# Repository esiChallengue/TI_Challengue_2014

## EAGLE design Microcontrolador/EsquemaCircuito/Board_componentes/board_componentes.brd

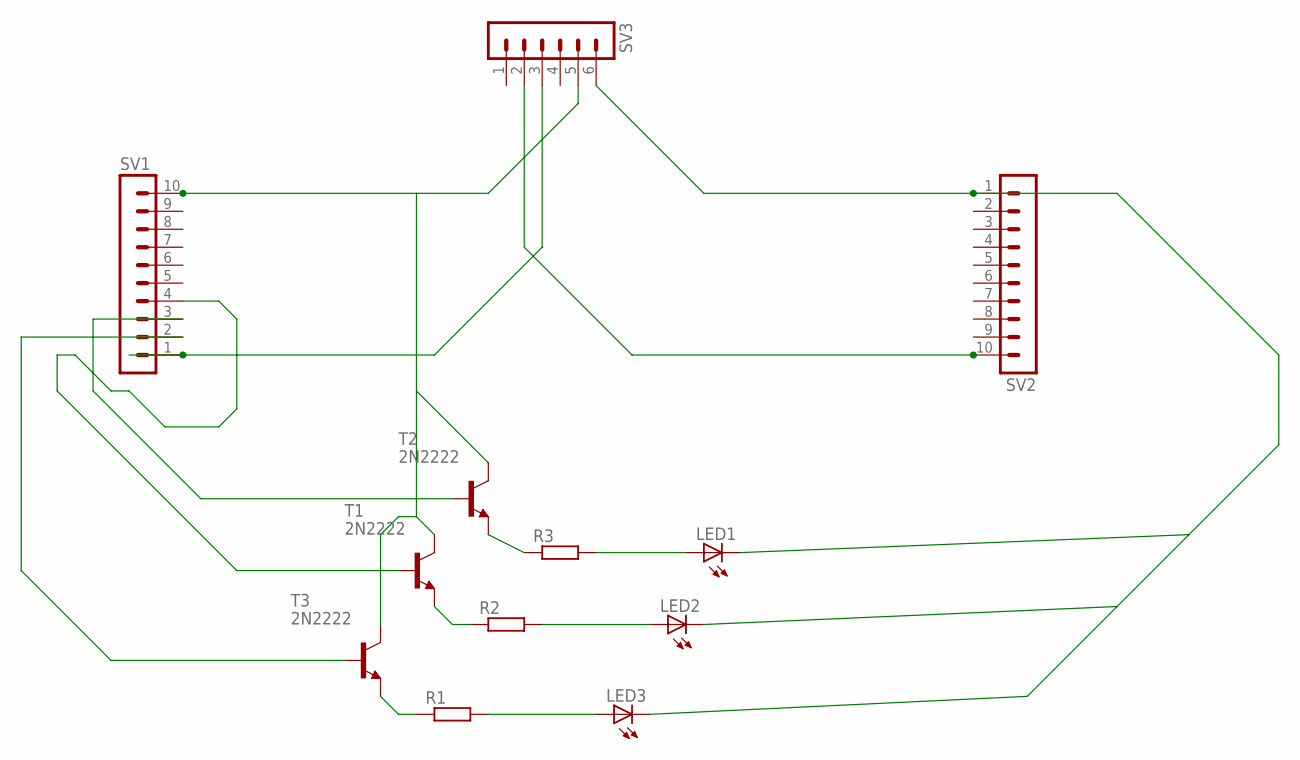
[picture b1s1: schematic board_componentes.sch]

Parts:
LED1, LED2, LED3: LED_ELD260; LED_LD260
R1, R2, R3: R-EU_0207/12; 0207/12
SV1, SV2: MA10-1
SV3: MA06-1
T1, T2, T3: 2N2222; TO18

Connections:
unnamed: LED1.K (C), LED2.K (C), LED3.K (C), SV2.1, SV3.6
unnamed: SV1.10, SV3.5, T1.3 (C), T2.3 (C), T3.3 (C)
unnamed: SV1.4, T1.2 (B)
unnamed: SV1.2, T3.2 (B)
unnamed: SV1.3, T2.2 (B)
unnamed: SV2.10, SV3.2
unnamed: R1.1, T3.1 (E)
unnamed: LED3.A, R1.2
unnamed: SV1.1, SV3.3
unnamed: LED1.A, R3.2
unnamed: LED2.A, R2.2
unnamed: R2.1, T1.1 (E)
unnamed: R3.1, T2.1 (E)

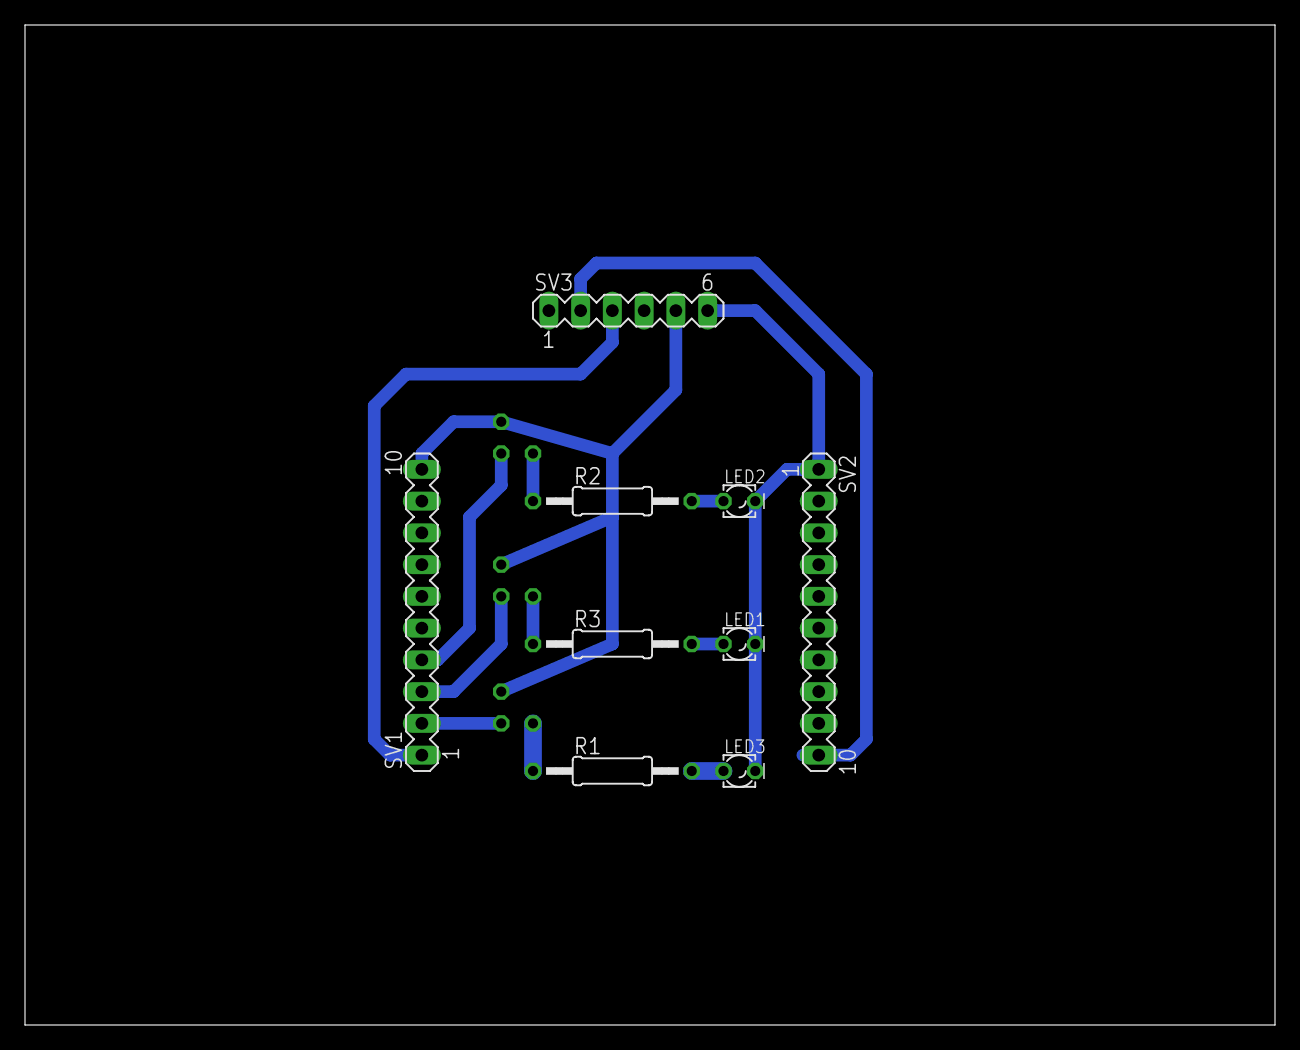
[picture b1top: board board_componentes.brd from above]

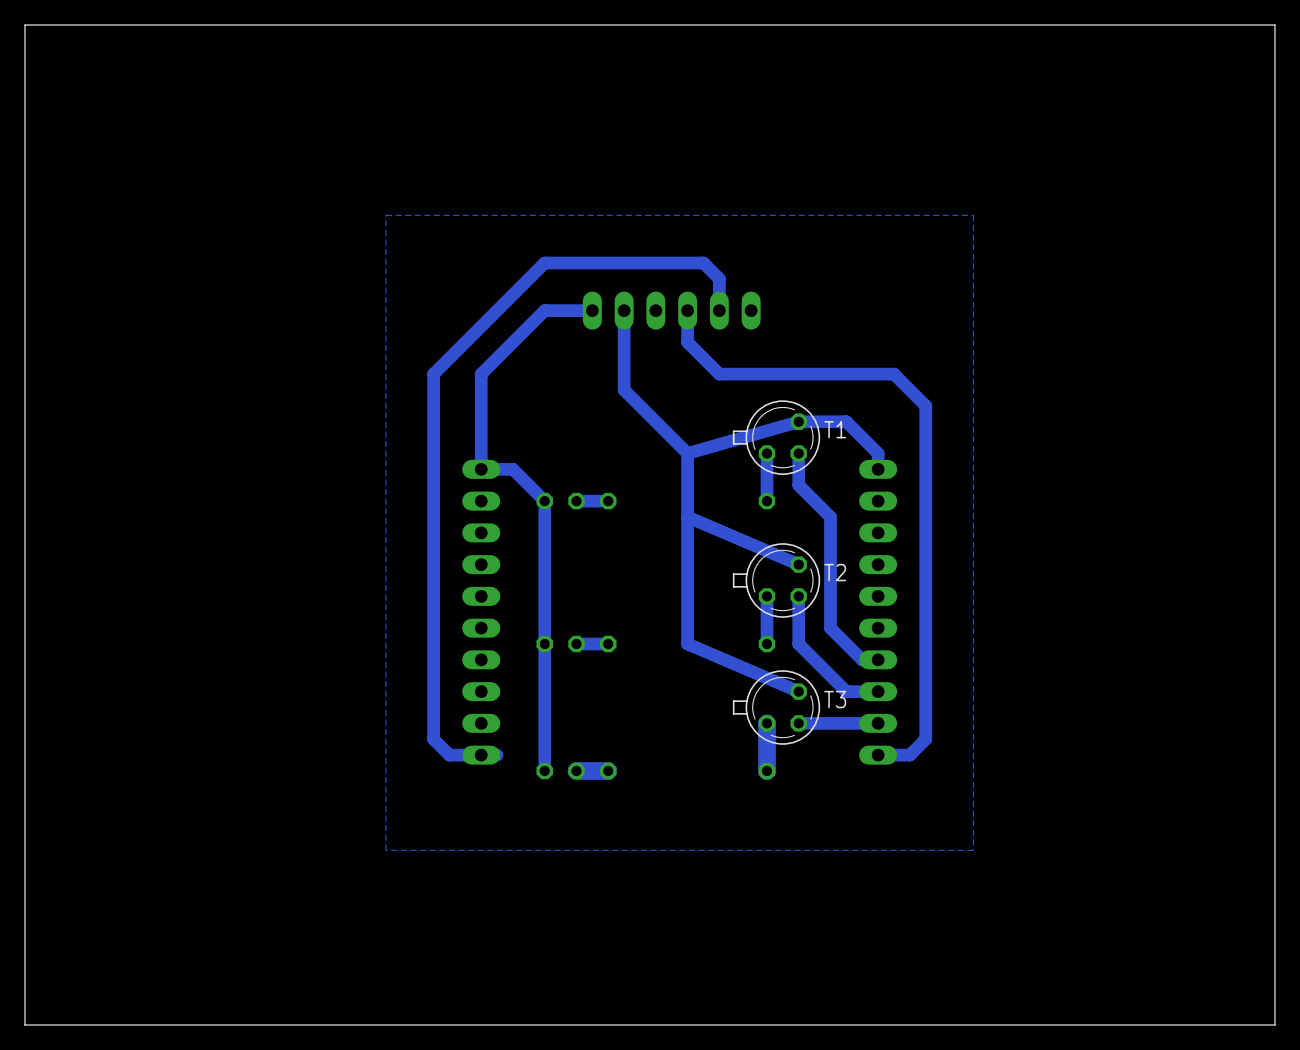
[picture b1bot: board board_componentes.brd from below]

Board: 2 copper layers, 100.0 x 80.0 mm, 12 parts (3 on the bottom side), 13 nets.

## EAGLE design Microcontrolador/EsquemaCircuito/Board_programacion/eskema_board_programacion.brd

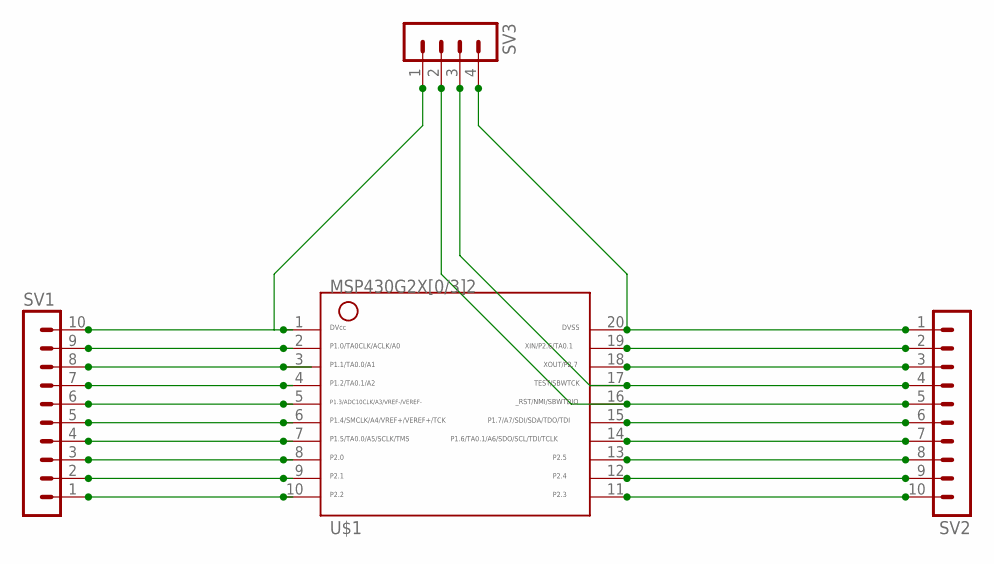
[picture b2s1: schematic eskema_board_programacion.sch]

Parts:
SV1, SV2: MA10-1
SV3: MA04-1
U$1: G2X[0/3]2---N20; N20

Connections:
unnamed: SV2.1, SV3.4, U$1.20
unnamed: SV1.9, U$1.2
unnamed: SV2.2, U$1.19
unnamed: SV2.3, U$1.18
unnamed: SV1.8, U$1.3
unnamed: SV2.4, SV3.3, U$1.17
unnamed: SV1.7, U$1.4
unnamed: SV2.5, SV3.2, U$1.16
unnamed: SV1.6, U$1.5
unnamed: SV2.6, U$1.15
unnamed: SV1.5, U$1.6
unnamed: SV2.7, U$1.14
unnamed: SV1.4, U$1.7
unnamed: SV2.8, U$1.13
unnamed: SV1.3, U$1.8
unnamed: SV2.9, U$1.12
unnamed: SV1.2, U$1.9
unnamed: SV2.10, U$1.11
unnamed: SV1.1, U$1.10
unnamed: SV1.10, SV3.1, U$1.1

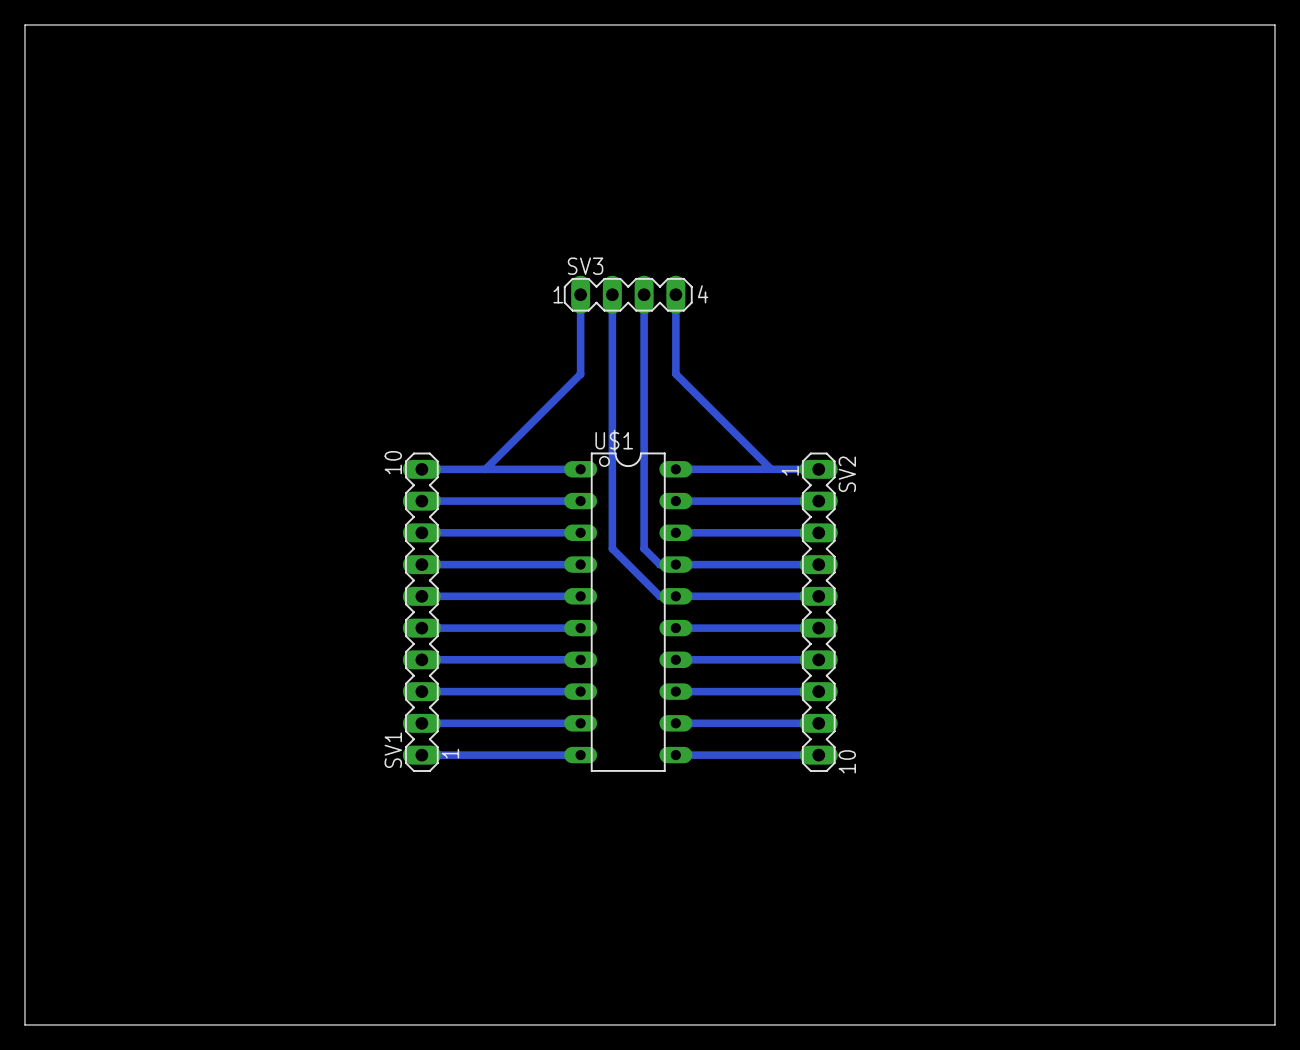
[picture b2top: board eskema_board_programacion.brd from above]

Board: 2 copper layers, 100.0 x 80.0 mm, 4 parts (0 on the bottom side), 20 nets.

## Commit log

2014-05-14 Ver 0.0
    Creación de directorios
2014-05-14 V 0.1
    Creación de archivos de texto
2014-05-14 V 0.3
    Agregado esquema de ideas y carpeta servidor
2014-05-14 v 0.4
    Creación de casi todos los ficheros restantes
2014-05-14 V 0.5
    Primera versión funcional del SERVIDOR PHP+MYSQL
2014-05-14 V 0.6
    Arreglo de explicaciones
2014-05-14 V 0.7
    Version prealpha aplicación android
2014-05-14 V 0.8
    Mejoras interfaz y errores en la app movil
2014-05-15 v 0.9
    Automaticamente detecta si están activados los chips de GPS y bluetooth,
    y crea cada 10 segundos un registro en el servidor
2014-05-15 V 0.9.1
    Corrección de sincronización de la version v0.9
2014-05-15 V 1.0
    Creada versión del firmware alpha del microcontrolador
2014-06-05 V 0.9.2
    Arreglado errores de posicionamiento GPS, envío de coordenadas
    codificadas en formato utf-8 al servidor, actualizada versión servidor
    para mostrar menos entradas
2014-06-06 V 0.9.3
    Agregado placa de apoyo para la pogramacion del MCU mediante ICSP
2014-06-06 V 0.9.4
    Fotos creación PCB apoyo del programador
2014-06-07 V 0.9.5
    Versión del servidor, que genera un tracking para mostrar el trazado en
    google_maps a partir de las ultimas X coordenadas, agregada versión
    nueva del AppMovil, autoconecta con el modulo bluetooth mediante una
    mac, y empieza la retransmisión de temperatura y coordenadas
2014-06-07 V 0.9.6
    Placa componentes, ** Imprimir como Mirrored!
2014-06-08 V 0.9.7
    Versión actualizada del microcontrolador
2014-06-08 V 0.9.8
    Control de reseteo del microchip por software
2014-06-08 V 0.9.9
    Versión 100% funcional de la apliación android
2014-06-09 V 1.0.1
    Version del servidor que soporta el seguimiento de multiples CHIPS, así
    como un autorefresco de la página cada 20 segundos y muestreo de una
    ruta por los mapas de google
2014-06-09 V 1.0.2
    Creado archivo TODO.txt
2014-06-09 V 1.0.3
    Primera Candidate Release de la versión del Servidor y del
    Microprocesador
2014-06-09 v 1.0.4
    Versión beta aplicación android (semi-final)
2014-06-09 v 1.0.5
    Pequeña modificación en la placa y el programa para reiniciar el
    bluetooth mediante software, ahora reinicia el bluetooth y el chip cada
    x ciclos que no recibe el paquete alive "a"
    Versión definitiva de la apliación movil, contiene un fallo que bloquea
    el MainThread, ahora se debuggeara y corregirá
2014-06-10 V 1.0.6
    Primera RELEASE CANDIDATE definitiva, ya no se congela la aplicación, el
    baudrate está a 19200, 0 bits paridad y 0 bits parada, conexión estable
    y gran alcance
2014-06-11 V 1.0.7
    Copia de Seguridad. Ultimos cambios
2014-06-18 V 1.0.8
    Versión de android que guarda los datos del operario, arreglado problema
    del servidor que siempre mostraba el ultimo mapa independientemente del
    tracking_number
2014-06-18 V 1.0.9
    Revisión general de todos los ficheros, pequeñas modificaciones
2014-06-19 V 1.1.0
    Nueva versión de la APP android, reoorganización del codigo, mejoras de
    estabilidad, boton reiniciar conexion
2014-06-20 V 1.1.1
    Nueva versión microcontrolador, mas estabilidad en el bluetooth, soporte
    para acelerometro, cambio de patrones en el envio al movil
2014-06-22 V 1.1.2
    Nueva versión web, modificación menor firmware chip, manual de
    acelerometro
2014-06-23 V 1.1.3
    Release Candidate
2014-07-10 V 1.1.4
    Reescritura semicompleta del modo conexión y gestion del bluetooth y los
    layouts :D
